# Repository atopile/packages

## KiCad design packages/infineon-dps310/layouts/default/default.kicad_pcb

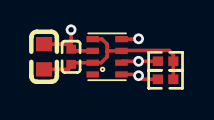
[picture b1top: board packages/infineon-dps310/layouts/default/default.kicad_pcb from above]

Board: 2 copper layers, 5 parts (0 on the bottom side), 4 nets.

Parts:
C1: {8.999..1.1}F; C0603
C2: 1±10.0%F; C0402
R1, R2: 4700±1.0%Ω; R0402
U1: LGA-8_DPS310XTSA1

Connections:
SCL: R1.1, U1.4
SDA: R2.1, U1.3
hv: C1.1, C2.1, R1.2, R2.2, U1.2, U1.6, U1.8
lv: C1.2, C2.2, U1.1, U1.5, U1.7

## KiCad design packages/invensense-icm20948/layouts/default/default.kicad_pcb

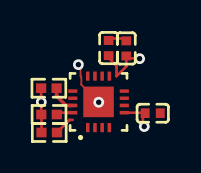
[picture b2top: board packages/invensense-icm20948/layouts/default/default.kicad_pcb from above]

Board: 2 copper layers, 7 parts (0 on the bottom side), 7 nets.

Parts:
C1, C3: 1±10.0%F; C0402
C2: {8.999..1.1}F; C0402
R1, R2, R3: 10000±1.0%Ω; R0402
U1: QFN-24_L3.0-W3.0-P0.40-BL-EP

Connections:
MOSI: R3.2, U1.24
RESV: U1.19, U1.20
hv: C3.1, R1.1, R2.1, R3.1, U1.8
lv: C1.2, C2.2, C3.2, U1.9, U1.18, U1.25
nCS: R1.2, U1.22
power_core_filter-power-hv: C1.1, C2.1, U1.13
spi-SCL: R2.2, U1.23
